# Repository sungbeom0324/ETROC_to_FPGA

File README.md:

## ETROC_to_FPGA Board

This board is designed to connect probe card for hybrid (LGAD+ETROC) sensor to FPGA (KC705) board. \
Reversible usage for debugging is also supported, by properly populating components (To be explained).

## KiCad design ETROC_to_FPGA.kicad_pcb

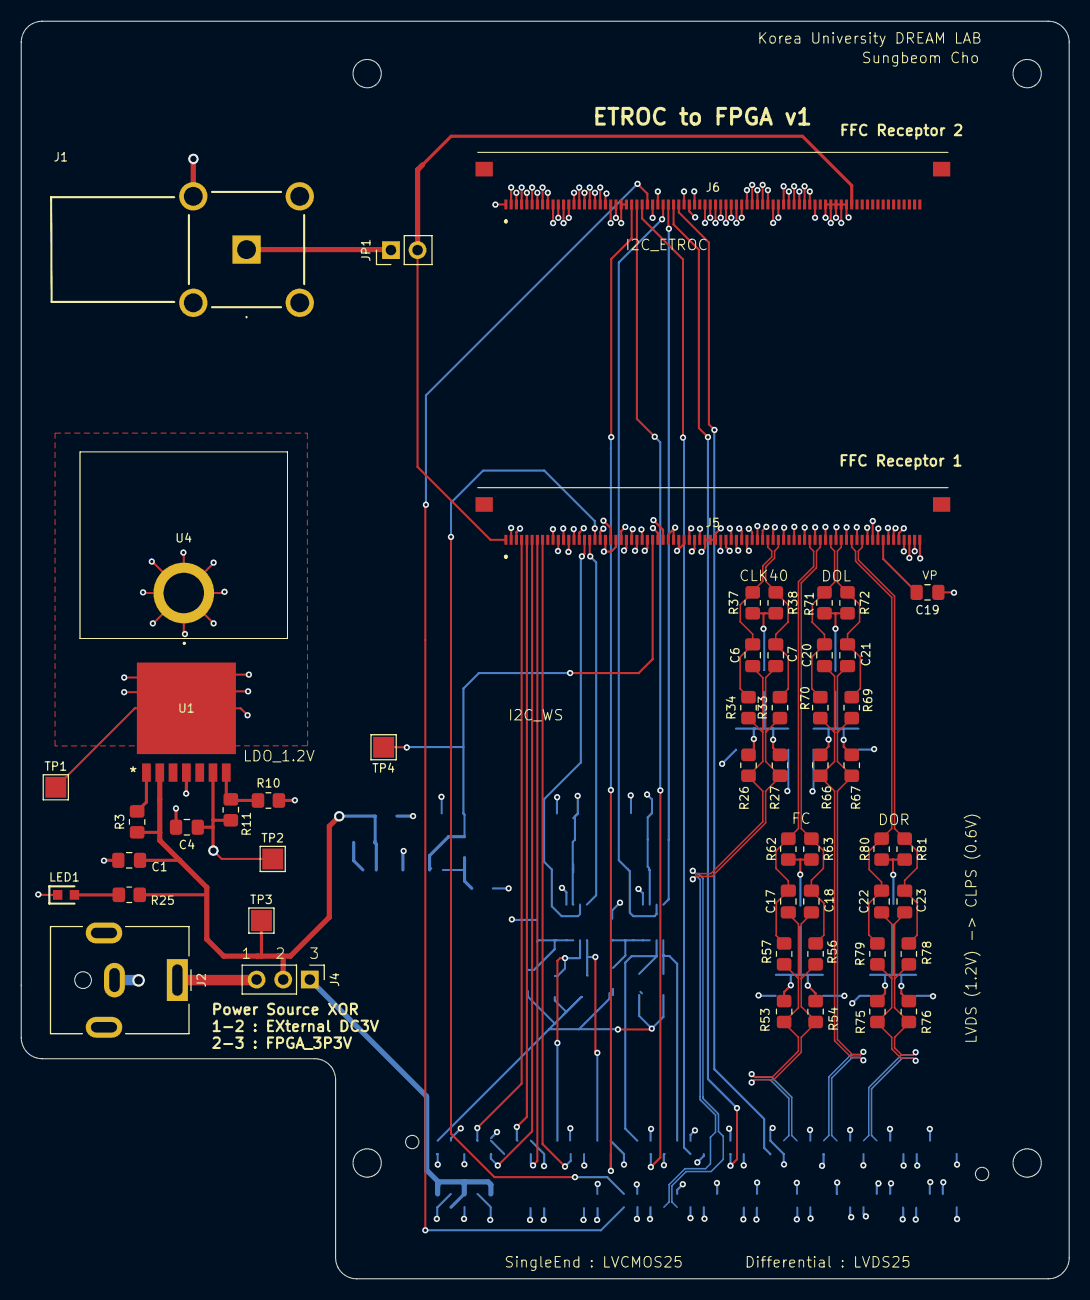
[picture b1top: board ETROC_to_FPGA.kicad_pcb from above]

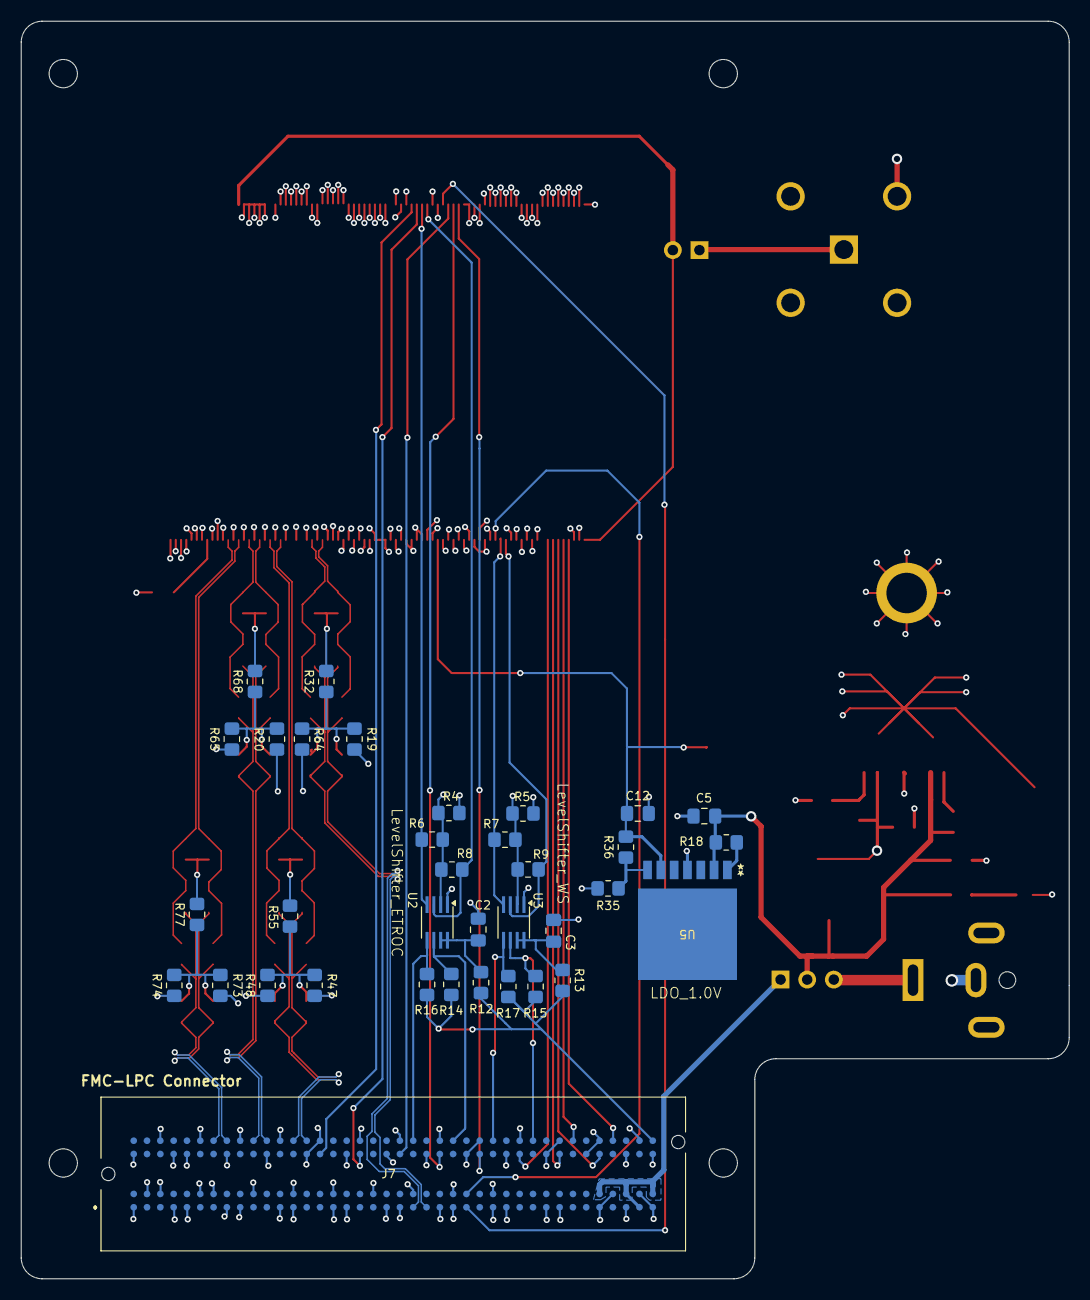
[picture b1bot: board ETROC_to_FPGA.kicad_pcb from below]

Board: 4 copper layers, 100.0 x 120.0 mm, 91 parts (35 on the bottom side), 61 nets.

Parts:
C1, C4, C5, C12: 10uF; C_0805_2012Metric_Pad1.18x1.45mm_HandSolder
C2, C3: 100pF; C_0805_2012Metric_Pad1.18x1.45mm_HandSolder
C6, C7, C17, C18, C20, C21, C22, C23: 100n; C_0805_2012Metric_Pad1.18x1.45mm_HandSolder
C19: 10n; C_0805_2012Metric_Pad1.18x1.45mm_HandSolder
Hole1, Hole2: MountingHole_2.7mm_M2.5
J1: Conn_Coaxial; BNCLRPC140
J2: Barrel_Jack; BarrelJack_CUI_PJ-063AH_Horizontal
J4: Conn_01x03; PinHeader_1x03_P2.54mm_Vertical
J5, J6: TF06L-80S-0.5SH_800_; TF06L80S05SH800
J7: ASP-134604-01; ASP13460401
JP1: Jumper_2_Open; PinHeader_1x02_P2.54mm_Vertical
LED1: LTST-C190KRKT; LEDC1608X80N
R3, R18: 100k; R_0805_2012Metric_Pad1.20x1.40mm_HandSolder
R4, R5: 240k; R_0805_2012Metric_Pad1.20x1.40mm_HandSolder
R6, R7, R8, R9, R14, R15, R16, R17, R26, R27, R53, R54, R66, R67, R75, R76: 2.2k; R_0805_2012Metric_Pad1.20x1.40mm_HandSolder
R10: 2k; R_0805_2012Metric_Pad1.20x1.40mm_HandSolder
R11, R35, R36: 2.8k; R_0805_2012Metric_Pad1.20x1.40mm_HandSolder
R12, R13: 200k; R_0805_2012Metric_Pad1.20x1.40mm_HandSolder
R19, R20, R47, R48, R64, R65, R73, R74: 1k; R_0805_2012Metric_Pad1.20x1.40mm_HandSolder
R25: 3.3k; R_0805_2012Metric_Pad1.20x1.40mm_HandSolder
R32, R33, R34, R55, R56, R57, R68, R69, R70, R77, R78, R79: 0; R_0805_2012Metric_Pad1.20x1.40mm_HandSolder
R37, R38, R62, R63, R71, R72, R80, R81: 50R; R_0805_2012Metric_Pad1.20x1.40mm_HandSolder
Spacer: MountingHole_2.7mm_M2.5
Spacer#2: MountingHole_2.7mm_M2.5
TP1: TP_GND; TestPoint_Pad_2.0x2.0mm
TP2: TP_1V2; TestPoint_Pad_2.0x2.0mm
TP3: TP_3V3; TestPoint_Pad_2.0x2.0mm
TP4: TP_1V0; TestPoint_Pad_2.0x2.0mm
U1, U5: MIC69502WR; S-PAK-7_MCH
U2, U3: PCA9306DCTR; SSOP-8_2.95x2.8mm_P0.65mm
U4: 504102B00000G

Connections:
/1.0V: C12.1, J5.29, R36.2, TP4.1 (1_1), U5.6 (VOUT)
/1.2V: C4.1, J5.3, J5.11, J5.13, J5.15, J5.20, J5.22, J5.30, J5.31, J5.32, J5.33, J5.34, J5.35, J5.44, J5.45, J5.46, J5.47, J5.48, J5.60, J5.62, J5.64, J5.74, J5.75, J5.76, J6.2, J6.3, J6.4, J6.5, J6.6, J6.7, J6.8, J6.9, J6.14, J6.15, J6.16, J6.17, J6.18, J6.19, J6.20, J6.30, J6.47, J6.48, J6.49, J6.50, J6.51, J6.54, J6.55, J6.56, J6.57, J6.58, J6.59, R4.2, R5.2, R6.1, R7.1, R8.1, R9.1, R11.2, R19.2, R47.2, R64.2, R73.2, TP2.1 (1_1), U1.6 (VOUT), U2.2 (VREF1), U3.2 (VREF1)
/2.5V: J7.H40, R12.1, R13.1, R14.1, R15.1, R16.1, R17.1
/3P3V: J4.1, J7.C39, J7.D36, J7.D38, J7.D40
/3V: J2.1, J4.3
/Bias: J5.1, J6.67, JP1.2 (B)
/Bias_IN: J1.1 (In), JP1.1 (A)
/CLK40_a_N: C7.1, J7.C23, R27.1, R33.1
/CLK40_a_P: C6.1, J7.C22, R26.1, R34.1
/CLK40_b_N: C7.2, J5.53, R33.2, R38.1
/CLK40_b_P: C6.2, J5.51, R34.2, R37.1
/DOL_a_N: C21.1, J7.H11, R67.1, R69.1
/DOL_a_P: C20.1, J7.H10, R66.1, R70.1
/DOL_b_N: C21.2, J5.65, R69.2, R72.1
/DOL_b_P: C20.2, J5.63, R70.2, R71.1
/DOR_a_N: C23.1, J7.H8, R76.1, R78.1
/DOR_a_P: C22.1, J7.H7, R75.1, R79.1
/DOR_b_N: C23.2, J5.69, R78.2, R81.1
/DOR_b_P: C22.2, J5.67, R79.2, R80.1
/FC_a_N: C18.1, J7.H14, R54.1, R56.1
/FC_a_P: C17.1, J7.H13, R53.1, R57.1
/FC_b_N: C18.2, J5.61, R56.2, R63.1
/FC_b_P: C17.2, J5.59, R57.2, R62.1
/I2C_ETR_ADD0: J6.25, J7.G27
/I2C_ETR_ADD1: J6.26, J7.G24
/I2C_ETR_ADD2: J6.27, J7.G21
/I2C_ETR_ADD3: J6.33, J7.G18
/I2C_ETR_ADD4: J6.34, J7.G15
/I2C_WS_ADD0: J5.8, J7.G30
/I2C_WS_ADD1: J5.7, J7.G33
/I2C_WS_ADD2: J5.6, J7.G36
/I2C_WS_ADD3: J5.5, J7.H34
/I2C_WS_ADD4: J5.4, J7.H37
/PWR_SRC: C1.1, C5.1, J4.2, R3.1, R18.1, R25.1, TP3.1 (1_1), U1.2 (VIN), U5.2 (VIN)
/RST_WS: J5.18, J7.D26
/RSTn: J6.28, J7.C26
/SCL_ETROC2: J6.31, R8.2, U2.3 (SCL1)
/SCL_ETROC2_FMC: J7.H25, R14.2, U2.6 (SCL2)
/SCL_WS: J5.16, R9.2, U3.3 (SCL1)
/SCL_WS_FMC: J7.H31, R15.2, U3.6 (SCL2)
/SDA_ETROC2: J6.32, R6.2, U2.4 (SDA1)
/SDA_ETROC2_FMC: J7.H22, R16.2, U2.5 (SDA2)
/SDA_WS: J5.17, R7.2, U3.4 (SDA1)
/SDA_WS_FMC: J7.H28, R17.2, U3.5 (SDA2)
/VP: C19.2, J5.73
GND: C1.2, C2.2, C3.2, C4.2, C5.2, C12.2, C19.1, J1.2 (Ext), J2.2, J5.2, J5.10, J5.12, J5.14, J5.19, J5.21, J5.23, J5.24, J5.25, J5.26, J5.27, J5.28, J5.36, J5.37, J5.38, J5.39, J5.40, J5.41, J5.42, J5.43, J5.49, J5.50, J5.52, J5.54, J5.56, J5.58, J5.66, J5.68, J5.70, J5.71, J5.72, J5.77, J5.78, J5.79, J5.80, J6.1, J6.10, J6.11, J6.12, J6.13, J6.21, J6.22, J6.23, J6.24, J6.29, J6.35, J6.36, J6.37, J6.39, J6.40, J6.41, J6.42, J6.43, J6.44, J6.45, J6.46, J6.52, J6.53, J6.60, J6.62, J6.63, J6.64, J6.65, J6.66, J7.C1, J7.C4, J7.C5, J7.C8, J7.C9, J7.C12, J7.C13, J7.C16, J7.C17, J7.C20, J7.C21, J7.C24, J7.C25, J7.C28, J7.C29, J7.C32, J7.C33, J7.C36, J7.C38, J7.C40, J7.D2, J7.D3, J7.D6, J7.D7, J7.D10, J7.D13, J7.D16, J7.D19, J7.D22, J7.D25, J7.D28, J7.D37, J7.D39, J7.G1, J7.G4, J7.G5, J7.G8, J7.G11, J7.G14, J7.G17, J7.G20, J7.G23, J7.G26, J7.G29, J7.G32, J7.G35, J7.G38, J7.G40, J7.H3, J7.H6, J7.H9, J7.H12, J7.H15, J7.H18, J7.H21, J7.H24, J7.H27, J7.H30, J7.H33, J7.H36, J7.H39, LED1.1 (K), R4.1, R5.1, R10.2, R20.1, R35.2, R48.1, R65.1, R74.1, TP1.1 (1_1), U1.4 (GND), U1.8 (EPAD), U2.1 (GND), U3.1 (GND), U4.1 (1_1), U5.4 (GND)
unnamed: LED1.2 (A), R25.2
unnamed: R19.1, R20.2, R26.2, R27.2, R32.1
unnamed: R32.2, R37.2, R38.2
unnamed: R47.1, R48.2, R53.2, R54.2, R55.1
unnamed: R55.2, R62.2, R63.2
unnamed: R64.1, R65.2, R66.2, R67.2, R68.1
unnamed: R68.2, R71.2, R72.2
unnamed: R73.1, R74.2, R75.2, R76.2, R77.1
unnamed: R77.2, R80.2, R81.2
unnamed: R10.1, R11.1, U1.7 (ADJ)
unnamed: R3.2, U1.1 (EN)
unnamed: C2.1, R12.2, U2.7 (VREF2), U2.8 (EN)
unnamed: C3.1, R13.2, U3.7 (VREF2), U3.8 (EN)
unnamed: R35.1, R36.1, U5.7 (ADJ)
unnamed: R18.2, U5.1 (EN)

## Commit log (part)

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2026-05-17 Initialize
2026-05-18 include images
